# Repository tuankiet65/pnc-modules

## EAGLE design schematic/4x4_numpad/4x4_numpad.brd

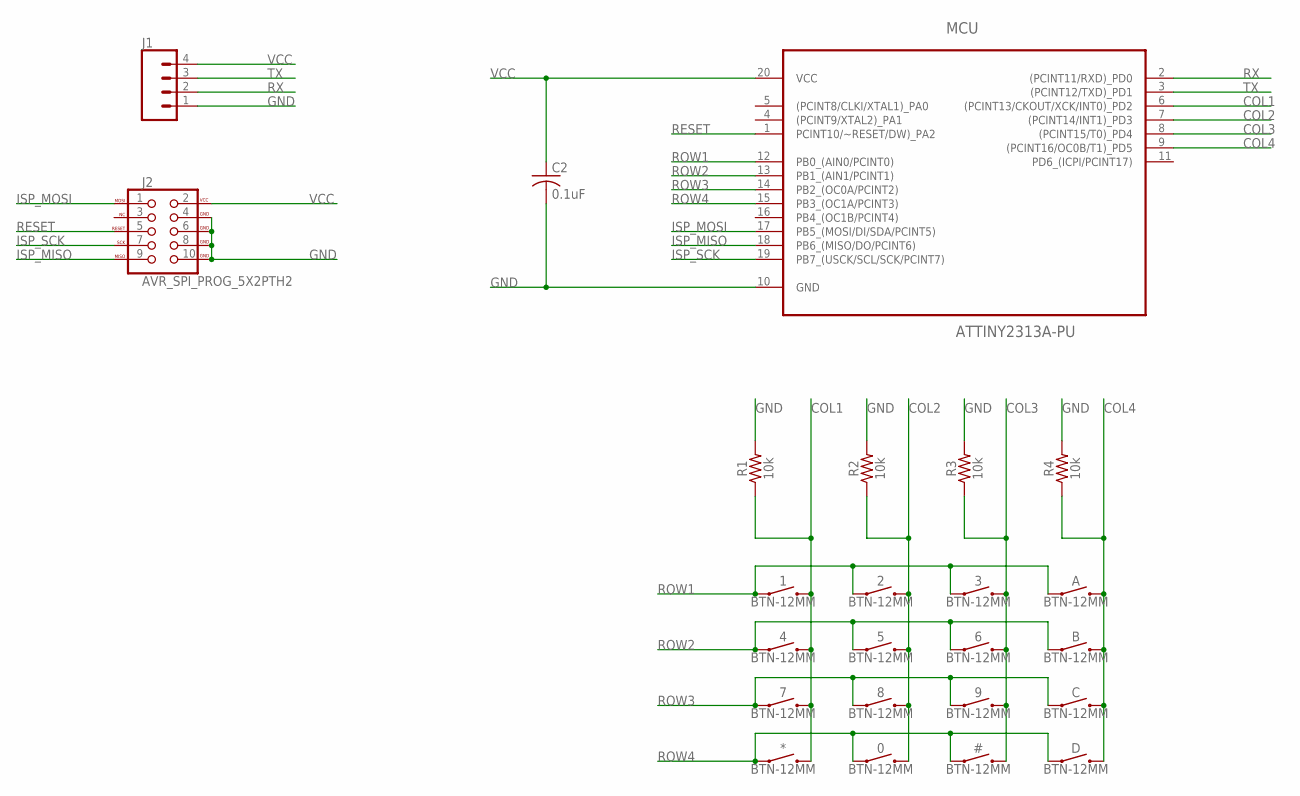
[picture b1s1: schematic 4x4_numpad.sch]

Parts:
0, 1, 2, 3, 4, 5, 6, 7, 8, 9: BTN-12MM; TACTILE_SWITCH_PTH_12MM
#: BTN-12MM; TACTILE_SWITCH_PTH_12MM
*: BTN-12MM; TACTILE_SWITCH_PTH_12MM
A: BTN-12MM; TACTILE_SWITCH_PTH_12MM
B: BTN-12MM; TACTILE_SWITCH_PTH_12MM
C: BTN-12MM; TACTILE_SWITCH_PTH_12MM
C2: 0.1uF; C050-025X075
D: BTN-12MM; TACTILE_SWITCH_PTH_12MM
J1: CONN_04; 1X04
J2: AVR_SPI_PROG_5X2PTH2; 2X5-SHROUDED
MCU: ATTINY2313A-PU; DIP254P762X533-20
R1, R2, R3, R4: 10k; AXIAL-0.3

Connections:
COL1: 1.3 (2), 1.4 (2), 4.3 (2), 4.4 (2), 7.3 (2), 7.4 (2), *.3 (2), *.4 (2), MCU.6 ((PCINT13/CKOUT/XCK/INT0)_PD2), R1.P$1 (1)
COL2: 0.3 (2), 0.4 (2), 2.3 (2), 2.4 (2), 5.3 (2), 5.4 (2), 8.3 (2), 8.4 (2), MCU.7 ((PCINT14/INT1)_PD3), R2.P$1 (1)
COL3: 3.3 (2), 3.4 (2), 6.3 (2), 6.4 (2), 9.3 (2), 9.4 (2), #.3 (2), #.4 (2), MCU.8 ((PCINT15/T0)_PD4), R3.P$1 (1)
COL4: A.3 (2), A.4 (2), B.3 (2), B.4 (2), C.3 (2), C.4 (2), D.3 (2), D.4 (2), MCU.9 ((PCINT16/OC0B/T1)_PD5), R4.P$1 (1)
GND: C2.2, J1.1, J2.4 (GND), J2.6 (GND), J2.8 (GND), J2.10 (GND), MCU.10 (GND), R1.P$2 (2), R2.P$2 (2), R3.P$2 (2), R4.P$2 (2)
ISP_MISO: J2.9 (MISO), MCU.18 (PB6_(MISO/DO/PCINT6))
ISP_MOSI: J2.1 (MOSI), MCU.17 (PB5_(MOSI/DI/SDA/PCINT5))
ISP_SCK: J2.7 (SCK), MCU.19 (PB7_(USCK/SCL/SCK/PCINT7))
RESET: J2.5 (RESET), MCU.1 (PCINT10/~RESET/DW)_PA2)
ROW1: 1.1, 1.2 (1), 2.1, 2.2 (1), 3.1, 3.2 (1), A.1, A.2 (1), MCU.12 (PB0_(AIN0/PCINT0))
ROW2: 4.1, 4.2 (1), 5.1, 5.2 (1), 6.1, 6.2 (1), B.1, B.2 (1), MCU.13 (PB1_(AIN1/PCINT1))
ROW3: 7.1, 7.2 (1), 8.1, 8.2 (1), 9.1, 9.2 (1), C.1, C.2 (1), MCU.14 (PB2_(OC0A/PCINT2))
ROW4: 0.1, 0.2 (1), #.1, #.2 (1), *.1, *.2 (1), D.1, D.2 (1), MCU.15 (PB3_(OC1A/PCINT3))
RX: J1.2, MCU.2 ((PCINT11/RXD)_PD0)
TX: J1.3, MCU.3 ((PCINT12/TXD)_PD1)
VCC: C2.1, J1.4, J2.2 (VCC), MCU.20 (VCC)

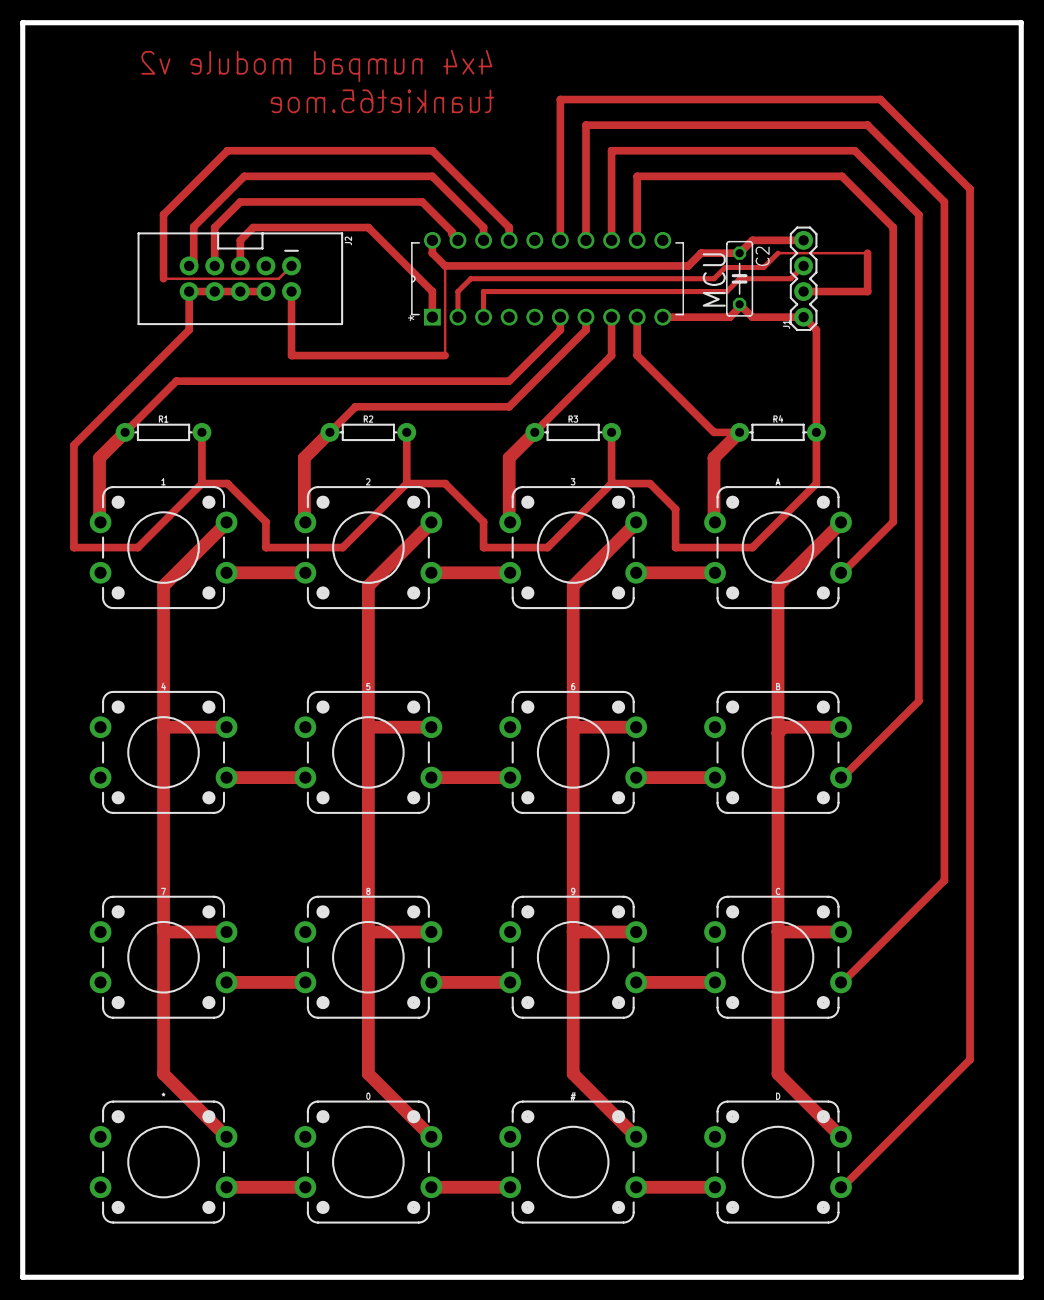
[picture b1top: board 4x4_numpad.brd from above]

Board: 2 copper layers, 99.1 x 124.5 mm, 24 parts (0 on the bottom side), 16 nets.

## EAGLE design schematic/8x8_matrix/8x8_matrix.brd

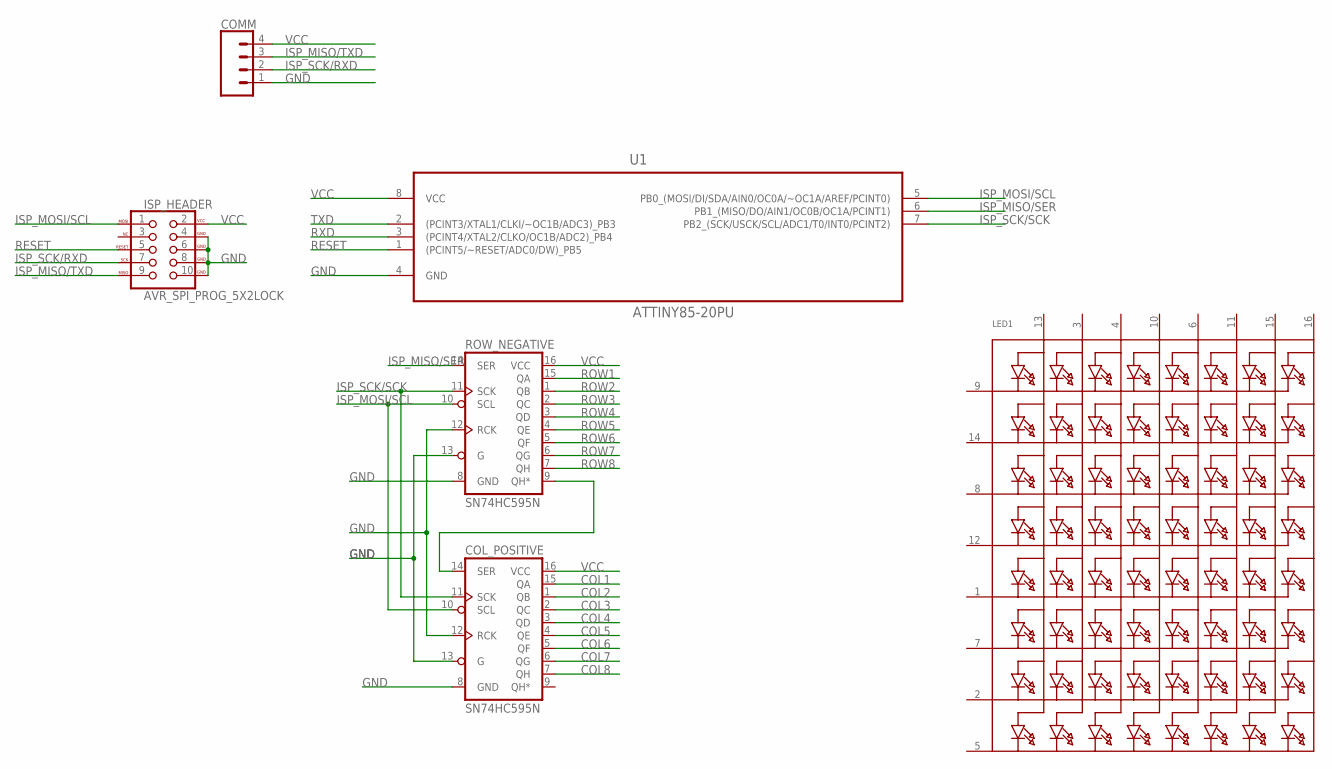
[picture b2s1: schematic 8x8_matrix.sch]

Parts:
COL_POSITIVE: SN74HC595N; DIP16
COMM: CONN_04POLAR; MOLEX-1X4
ISP_HEADER: AVR_SPI_PROG_5X2LOCK; 2X5-SHROUDED_LOCK
LED1: SEGMENT_8X8_ROWCATHODEM12A881UR; SEGMENT_BL-M12A881UR
ROW_NEGATIVE: SN74HC595N; DIP16
U1: ATTINY85-20PU; DIP254P762X533-8

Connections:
COL1: COL_POSITIVE.15 (QA)
COL2: COL_POSITIVE.1 (QB)
COL3: COL_POSITIVE.2 (QC)
COL4: COL_POSITIVE.3 (QD)
COL5: COL_POSITIVE.4 (QE)
COL6: COL_POSITIVE.5 (QF)
COL7: COL_POSITIVE.6 (QG)
COL8: COL_POSITIVE.7 (QH)
GND: COL_POSITIVE.8 (GND), COL_POSITIVE.12 (RCK), COL_POSITIVE.13 (G), COMM.1, ISP_HEADER.4 (GND), ISP_HEADER.6 (GND), ISP_HEADER.8 (GND), ISP_HEADER.10 (GND), ROW_NEGATIVE.8 (GND), ROW_NEGATIVE.12 (RCK), ROW_NEGATIVE.13 (G), U1.4 (GND)
ISP_MISO/SER: ROW_NEGATIVE.14 (SER), U1.6 (PB1_(MISO/DO/AIN1/OC0B/OC1A/PCINT1))
ISP_MISO/TXD: COMM.3, ISP_HEADER.9 (MISO)
ISP_MOSI/SCL: COL_POSITIVE.10 (SCL), ISP_HEADER.1 (MOSI), ROW_NEGATIVE.10 (SCL), U1.5 (PB0_(MOSI/DI/SDA/AIN0/OC0A/~OC1A/AREF/P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)
ISP_SCK/RXD: COMM.2, ISP_HEADER.7 (SCK)
ISP_SCK/SCK: COL_POSITIVE.11 (SCK), ROW_NEGATIVE.11 (SCK), U1.7 (PB2_(SCK/USCK/SCL/ADC1/T0/INT0/PCINT2))
unnamed: COL_POSITIVE.14 (SER), ROW_NEGATIVE.9 (QH*)
RESET: ISP_HEADER.5 (RESET), U1.1 ((PCINT5/~RESET/ADC0/DW)_PB5)
ROW1: ROW_NEGATIVE.15 (QA)
ROW2: ROW_NEGATIVE.1 (QB)
ROW3: ROW_NEGATIVE.2 (QC)
ROW4: ROW_NEGATIVE.3 (QD)
ROW5: ROW_NEGATIVE.4 (QE)
ROW6: ROW_NEGATIVE.5 (QF)
ROW7: ROW_NEGATIVE.6 (QG)
ROW8: ROW_NEGATIVE.7 (QH)
RXD: U1.3 ((PCINT4/XTAL2/CLKO/OC1B/ADC2)_PB4)
TXD: U1.2 ((PCINT3/XTAL1/CLKI/~OC1B/ADC3)_PB3)
VCC: COL_POSITIVE.16 (VCC), COMM.4, ISP_HEADER.2 (VCC), ROW_NEGATIVE.16 (VCC), U1.8 (VCC)

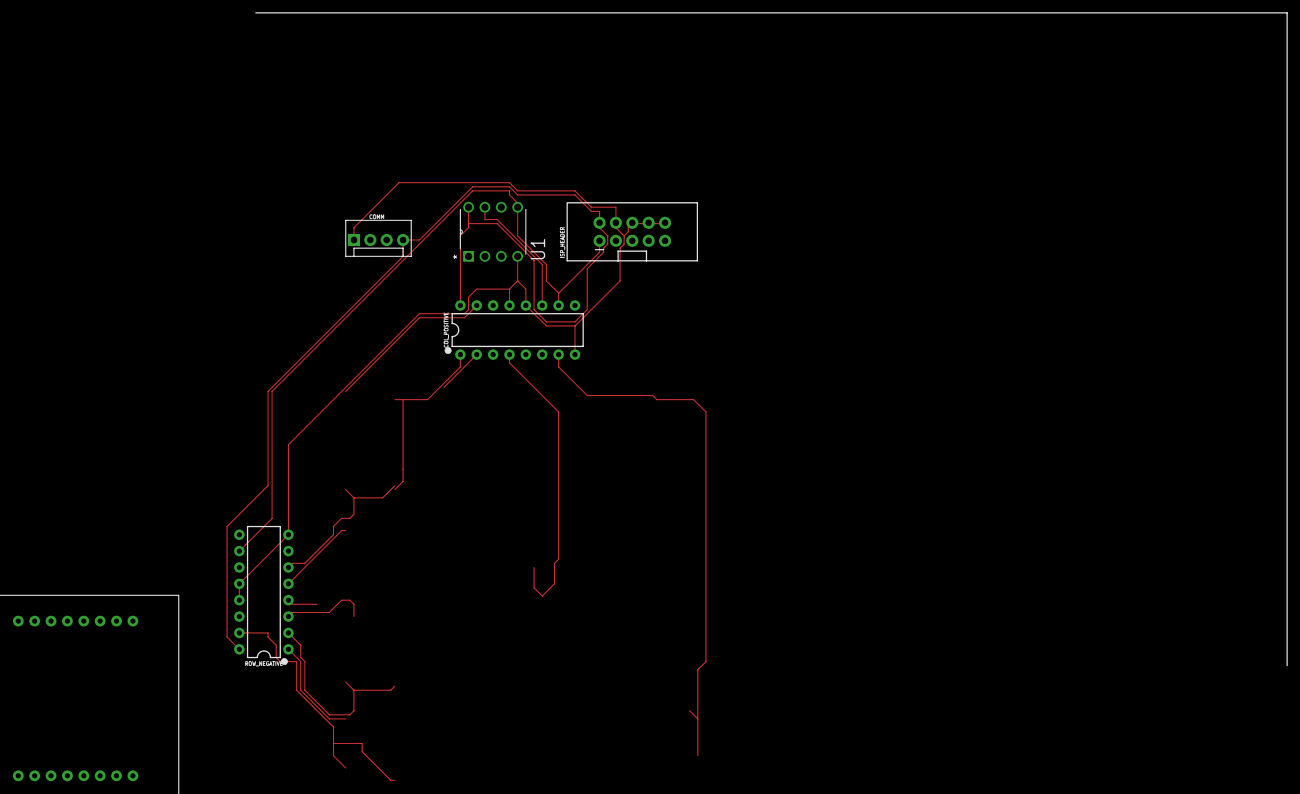
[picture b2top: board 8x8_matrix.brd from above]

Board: 2 copper layers, 160.0 x 101.3 mm, 6 parts (0 on the bottom side), 9 nets.

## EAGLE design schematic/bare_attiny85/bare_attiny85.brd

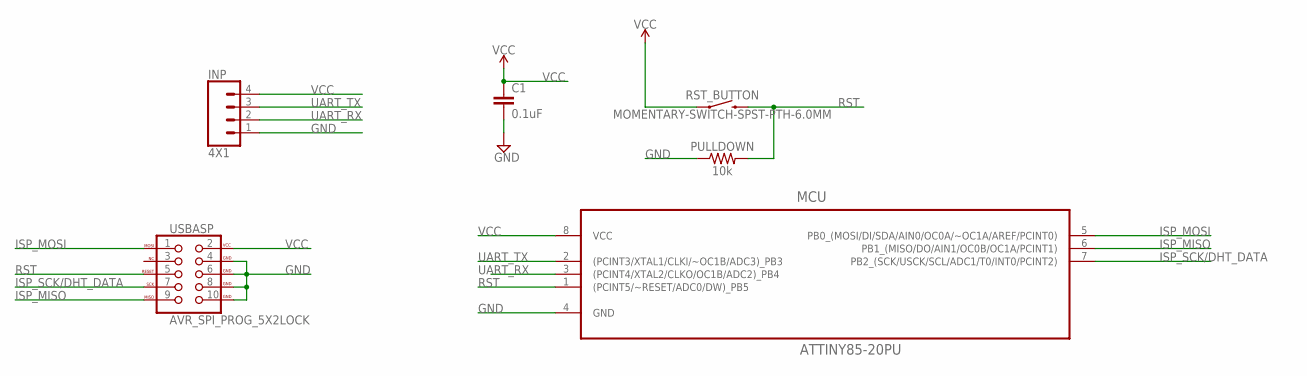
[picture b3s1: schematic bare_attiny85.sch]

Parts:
C1: 0.1uF; CAP-PTH-SMALL-KIT
INP: 4X1; 1X04
MCU: ATTINY85-20PU; DIP254P762X533-8
PULLDOWN: 10k; AXIAL-0.3
RST_BUTTON: MOMENTARY-SWITCH-SPST-PTH-6.0MM; TACTILE_SWITCH_PTH_6.0MM
USBASP: AVR_SPI_PROG_5X2LOCK; 2X5-SHROUDED_LOCK

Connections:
GND: C1.2, INP.1, MCU.4 (GND), PULLDOWN.P$1 (1), USBASP.4 (GND), USBASP.6 (GND), USBASP.8 (GND), USBASP.10 (GND)
ISP_MISO: MCU.6 (PB1_(MISO/DO/AIN1/OC0B/OC1A/PCINT1)), USBASP.9 (MISO)
ISP_MOSI: MCU.5 (PB0_(MOSI/DI/SDA/AIN0/OC0A/~OC1A/AREF/P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), USBASP.1 (MOSI)
ISP_SCK/DHT_DATA: MCU.7 (PB2_(SCK/USCK/SCL/ADC1/T0/INT0/PCINT2)), USBASP.7 (SCK)
RST: MCU.1 ((PCINT5/~RESET/ADC0/DW)_PB5), PULLDOWN.P$2 (2), RST_BUTTON.3 (2), USBASP.5 (RESET)
UART_RX: INP.2, MCU.3 ((PCINT4/XTAL2/CLKO/OC1B/ADC2)_PB4)
UART_TX: INP.3, MCU.2 ((PCINT3/XTAL1/CLKI/~OC1B/ADC3)_PB3)
VCC: C1.1, INP.4, MCU.8 (VCC), RST_BUTTON.1, USBASP.2 (VCC)

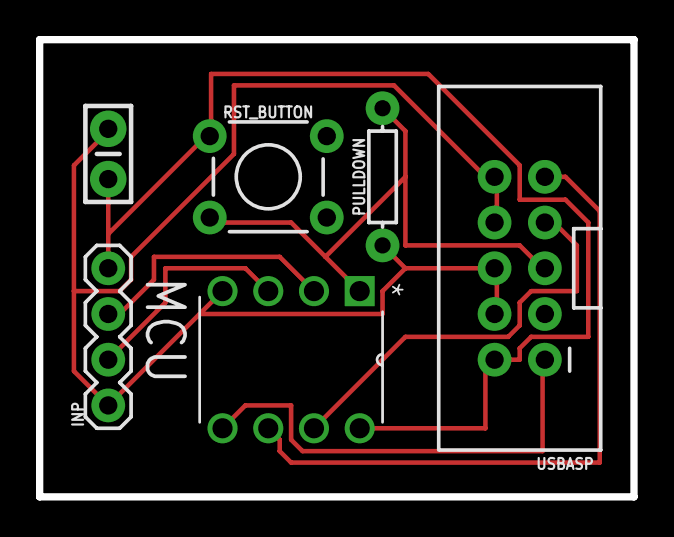
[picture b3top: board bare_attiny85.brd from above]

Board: 2 copper layers, 33.0 x 25.4 mm, 6 parts (0 on the bottom side), 8 nets.

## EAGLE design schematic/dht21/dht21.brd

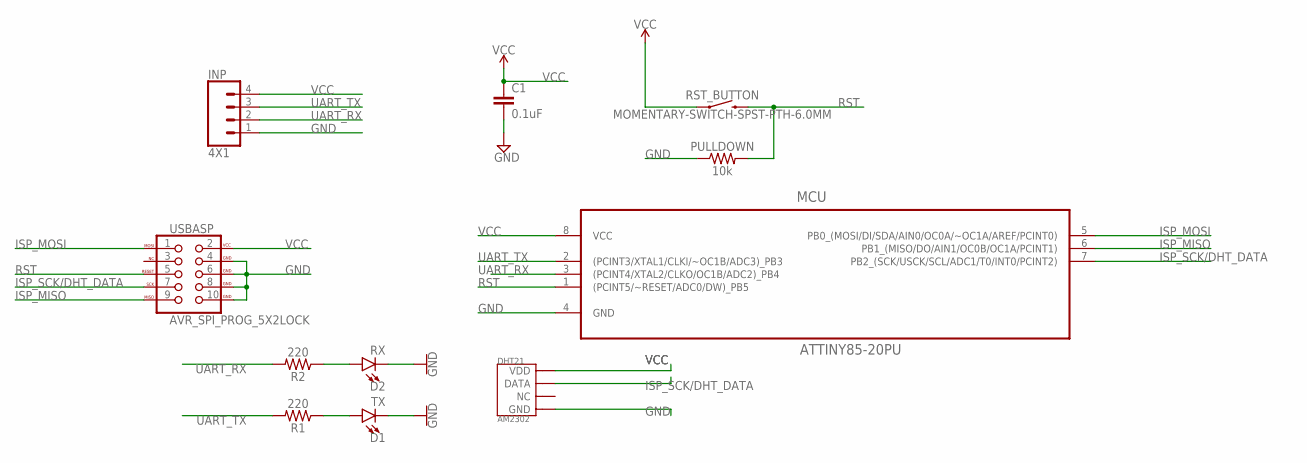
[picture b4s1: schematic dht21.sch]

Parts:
C1: 0.1uF; CAP-PTH-SMALL-KIT
D1: TX; LED_3MM
D2: RX; LED_3MM
DHT21: AM2302; SNR4-2.54-25.0X15.0X7.0MM
INP: 4X1; 1X04
MCU: ATTINY85-20PU; DIP254P762X533-8
PULLDOWN: 10k; AXIAL-0.3
R1, R2: 220; AXIAL-0.3
RST_BUTTON: MOMENTARY-SWITCH-SPST-PTH-6.0MM; TACTILE_SWITCH_PTH_6.0MM
USBASP: AVR_SPI_PROG_5X2LOCK; 2X5-SHROUDED_LOCK

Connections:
GND: C1.2, D1.K (C), D2.K (C), DHT21.P$4 (GND), INP.1, MCU.4 (GND), PULLDOWN.P$1 (1), USBASP.4 (GND), USBASP.6 (GND), USBASP.8 (GND), USBASP.10 (GND)
ISP_MISO: MCU.6 (PB1_(MISO/DO/AIN1/OC0B/OC1A/PCINT1)), USBASP.9 (MISO)
ISP_MOSI: MCU.5 (PB0_(MOSI/DI/SDA/AIN0/OC0A/~OC1A/AREF/P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), USBASP.1 (MOSI)
ISP_SCK/DHT_DATA: DHT21.P$2 (DATA), MCU.7 (PB2_(SCK/USCK/SCL/ADC1/T0/INT0/PCINT2)), USBASP.7 (SCK)
unnamed: D1.A, R1.P$1 (1)
unnamed: D2.A, R2.P$1 (1)
RST: MCU.1 ((PCINT5/~RESET/ADC0/DW)_PB5), PULLDOWN.P$2 (2), RST_BUTTON.3 (2), USBASP.5 (RESET)
UART_RX: INP.2, MCU.3 ((PCINT4/XTAL2/CLKO/OC1B/ADC2)_PB4), R2.P$2 (2)
UART_TX: INP.3, MCU.2 ((PCINT3/XTAL1/CLKI/~OC1B/ADC3)_PB3), R1.P$2 (2)
VCC: C1.1, DHT21.P$1 (VDD), INP.4, MCU.8 (VCC), RST_BUTTON.1, USBASP.2 (VCC)

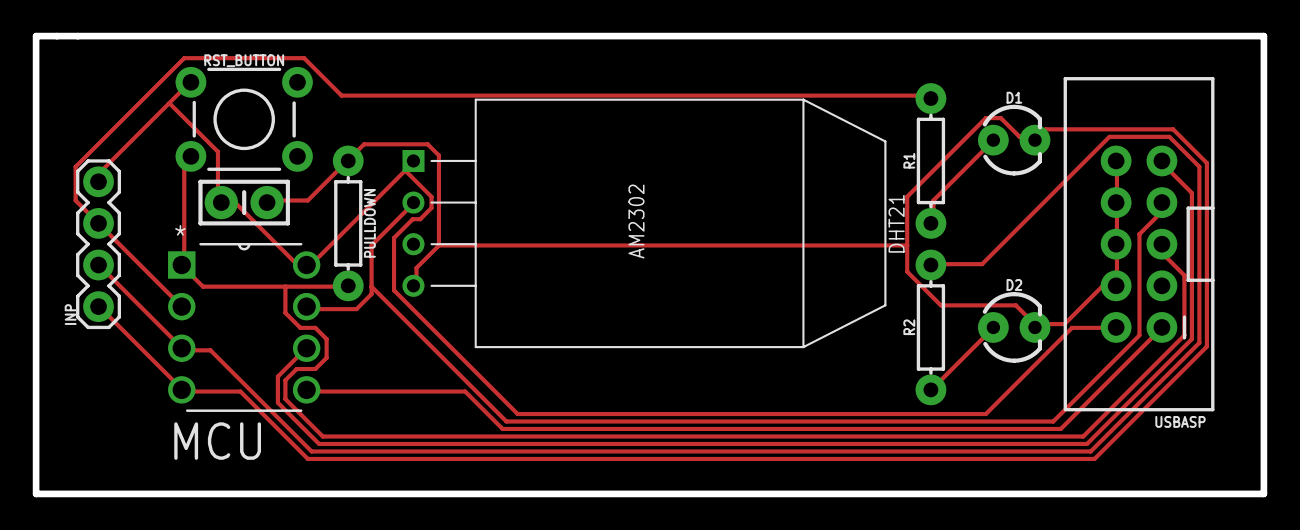
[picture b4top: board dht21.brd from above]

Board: 2 copper layers, 74.9 x 27.9 mm, 11 parts (0 on the bottom side), 10 nets.

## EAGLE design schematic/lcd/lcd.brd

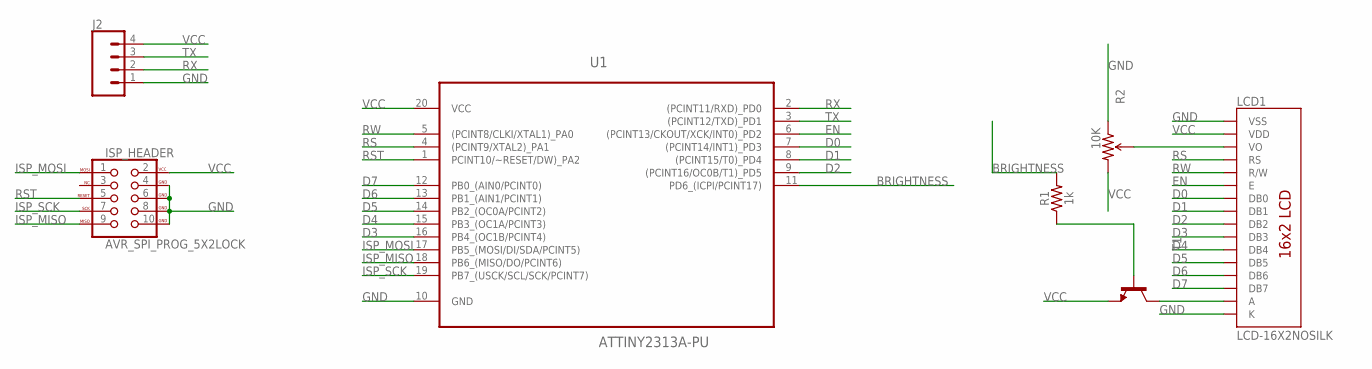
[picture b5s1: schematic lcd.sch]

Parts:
ISP_HEADER: AVR_SPI_PROG_5X2LOCK; 2X5-SHROUDED_LOCK
J2: CONN_04; 1X04
LCD1: LCD-16X2NOSILK; LCD-16X2_NOSILK
R1: 1k; AXIAL-0.3
R2: 10K; TRIM_POT_PTH
T1: -NPN-TO92-ECB; TO92-ECB
U1: ATTINY2313A-PU; DIP254P762X533-20

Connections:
BRIGHTNESS: R1.P$2 (2), U1.11 (PD6_(ICPI/PCINT17))
CONTRAST: LCD1.3 (VO), R2.2 (WIPER)
D0: LCD1.7 (DB0), U1.7 ((PCINT14/INT1)_PD3)
D1: LCD1.8 (DB1), U1.8 ((PCINT15/T0)_PD4)
D2: LCD1.9 (DB2), U1.9 ((PCINT16/OC0B/T1)_PD5)
D3: LCD1.10 (DB3), U1.16 (PB4_(OC1B/PCINT4))
D4: LCD1.11 (DB4), U1.15 (PB3_(OC1A/PCINT3))
D5: LCD1.12 (DB5), U1.14 (PB2_(OC0A/PCINT2))
D6: LCD1.13 (DB6), U1.13 (PB1_(AIN1/PCINT1))
D7: LCD1.14 (DB7), U1.12 (PB0_(AIN0/PCINT0))
EN: LCD1.6 (E), U1.6 ((PCINT13/CKOUT/XCK/INT0)_PD2)
GND: ISP_HEADER.4 (GND), ISP_HEADER.6 (GND), ISP_HEADER.8 (GND), ISP_HEADER.10 (GND), J2.1, LCD1.1 (VSS), LCD1.16 (K), R2.1 (CCW), U1.10 (GND)
ISP_MISO: ISP_HEADER.9 (MISO), U1.18 (PB6_(MISO/DO/PCINT6))
ISP_MOSI: ISP_HEADER.1 (MOSI), U1.17 (PB5_(MOSI/DI/SDA/PCINT5))
ISP_SCK: ISP_HEADER.7 (SCK), U1.19 (PB7_(USCK/SCL/SCK/PCINT7))
unnamed: LCD1.15 (A), T1.C
unnamed: R1.P$1 (1), T1.B
RS: LCD1.4 (RS), U1.4 ((PCINT9/XTAL2)_PA1)
RST: ISP_HEADER.5 (RESET), U1.1 (PCINT10/~RESET/DW)_PA2)
RW: LCD1.5 (R/W), U1.5 ((PCINT8/CLKI/XTAL1)_PA0)
RX: J2.2, U1.2 ((PCINT11/RXD)_PD0)
TX: J2.3, U1.3 ((PCINT12/TXD)_PD1)
VCC: ISP_HEADER.2 (VCC), J2.4, LCD1.2 (VDD), R2.3 (CW), T1.E, U1.20 (VCC)

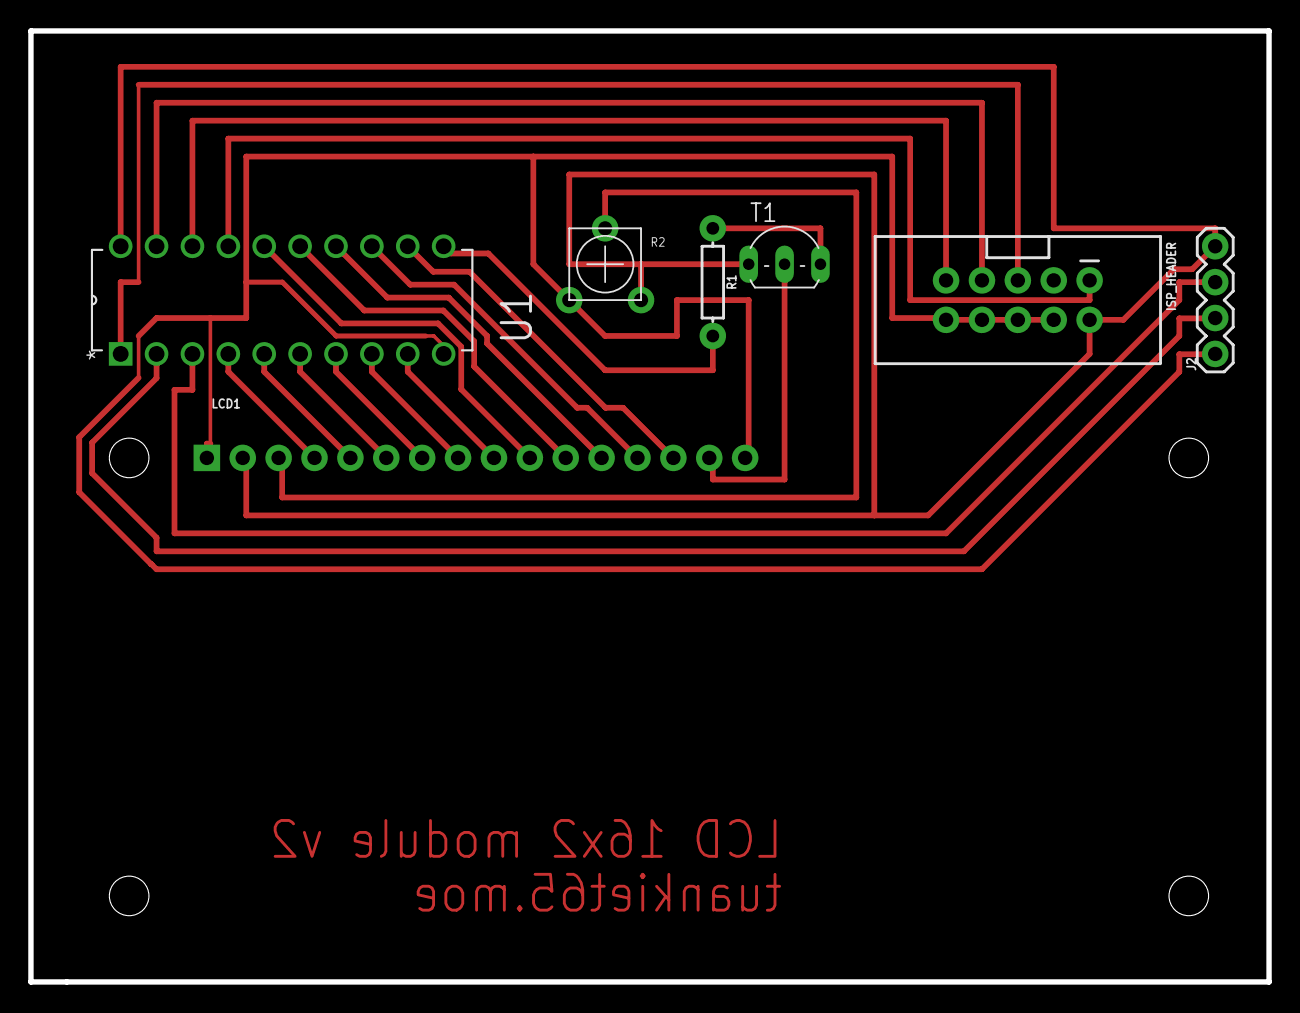
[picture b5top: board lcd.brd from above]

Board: 2 copper layers, 87.6 x 67.3 mm, 7 parts (0 on the bottom side), 23 nets.

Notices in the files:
parts and their libraries:
SparkFun-Resistors: Licensing: Creative Commons ShareAlike 4.0 International - https://creativecommons.org/licenses/by-sa/4.0
